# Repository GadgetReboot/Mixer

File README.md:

# Mixer
Simple op amp audio mixer for small audio experiments

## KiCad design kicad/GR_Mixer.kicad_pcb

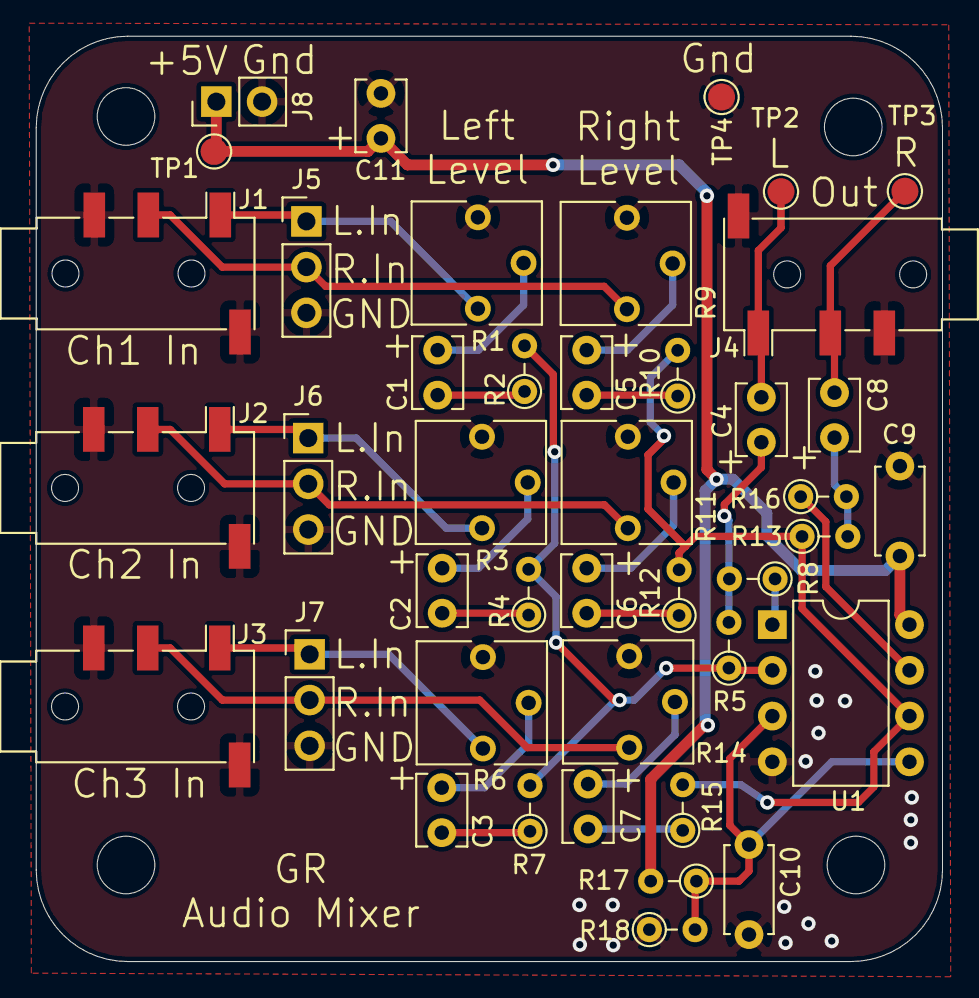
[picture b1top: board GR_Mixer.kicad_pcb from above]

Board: 2 copper layers, 50.3 x 51.4 mm, 46 parts (0 on the bottom side), 29 nets.

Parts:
C1, C2, C3, C4, C5, C6, C7, C8: 10uF; C_Disc_D3.8mm_W2.6mm_P2.50mm
C9, C10: 100nF; C_Disc_D4.7mm_W2.5mm_P5.00mm
C11: 4.7uF; C_Disc_D3.8mm_W2.6mm_P2.50mm
J1, J4: Ch 1 In; Jack_3.5mm_PJ320D_Horizontal
J2: Ch 2 In; Jack_3.5mm_PJ320D_Horizontal
J3: Ch 3 In; Jack_3.5mm_PJ320D_Horizontal
J5, J6, J7: Conn_01x03; PinHeader_1x03_P2.54mm_Vertical
J8: Conn_01x02; PinHeader_1x02_P2.54mm_Vertical
MH1, MH2, MH3, MH4: MountingHole; MountingHole_3.2mm_M3
R1, R3, R6, R9, R11, R14: 10K; Potentiometer_Vishay_T73YP_Vertical
R2, R4, R7, R10, R12, R15, R17: 10K; R_Axial_DIN0204_L3.6mm_D1.6mm_P2.54mm_Vertical
R5, R13: 3K3; R_Axial_DIN0204_L3.6mm_D1.6mm_P2.54mm_Vertical
R8, R16: 100r; R_Axial_DIN0204_L3.6mm_D1.6mm_P2.54mm_Vertical
R18: 4K3; R_Axial_DIN0204_L3.6mm_D1.6mm_P2.54mm_Vertical
TP1, TP2, TP3, TP4: TestPoint; TestPoint_Pad_D1.5mm
U1: LM358; DIP-8_W7.62mm

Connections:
+5V: C9.1, C11.1, J8.1, R17.2, TP1.1, U1.8
/L1_In: J1.T, J5.1, R1.1
/L2_In: J2.T, J6.1, R3.1
/L3_In: J3.T, J7.1, R6.1
/Left_Out: C4.1, J4.T, TP2.1
/R1_In: J1.R1, J5.2, R9.1
/R2_In: J2.R1, J6.2, R11.1
/R3_In: J3.R1, J7.2, R14.1
/Right_Out: C8.1, J4.R1, TP3.1
/Vbias: C10.1, R17.1, R18.2, U1.3, U1.5
GNDREF: C9.2, C10.2, C11.2, J1.R2, J1.S, J2.R2, J2.S, J3.R2, J3.S, J4.R2, J4.S, J5.3, J6.3, J7.3, J8.2, R1.3, R3.3, R6.3, R9.3, R11.3, R14.3, R18.1, TP4.1, U1.4
unnamed: C1.1, R2.1
unnamed: C1.2, R1.2
unnamed: C2.1, R4.1
unnamed: C2.2, R3.2
unnamed: C3.1, R7.1
unnamed: C3.2, R6.2
unnamed: C4.2, R5.2, R8.2
unnamed: C5.1, R10.1
unnamed: C5.2, R9.2
unnamed: C6.1, R12.1
unnamed: C6.2, R11.2
unnamed: C7.1, R15.1
unnamed: C7.2, R14.2
unnamed: C8.2, R13.2, R16.2
unnamed: R2.2, R4.2, R5.1, R7.2, U1.2
unnamed: R8.1, U1.1
unnamed: R10.2, R12.2, R13.1, R15.2, U1.6
unnamed: R16.1, U1.7
